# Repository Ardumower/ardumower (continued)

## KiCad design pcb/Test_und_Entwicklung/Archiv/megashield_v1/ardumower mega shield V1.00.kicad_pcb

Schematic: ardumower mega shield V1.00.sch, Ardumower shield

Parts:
C1, C2: 10uF
D1: LED
D2: MBR1045 schotky
D3: 5V
D4: 24V
D5: 1N4007
Dual1: MC33926
F1: FUSE
HC5: HC05_MODULE_ARDUMOWER_
JP1: JUMPER
K1: Tilt sens
P1: Perimeter
P2: Motor driver
P3: Bat charge
P4, P19: Mow Motor
P5: Motor sens
P6: Sonar C
P7: Sonar R
P8: Sonar L
P9: RC Remote
P10: ODO Left
P11: ODO Right
P12: User switch
P13: Lawn sens
P14: GPS RX
P15: DC/DC
P16: I2C
P17: Bumper
P18: 24V in
P20: SW_LED
P21: UART1
Q1: IRLIZ44N
R1, R6: 470R
R2, R4: 47K
R3, R5: 5K
R7, R8: 1K
R9, R10: 2M2
R11: 180
R12: 10K
R13: 470r
R14: 2k2
SHIELD1: ARDUINO_MEGA_SHIELD
SP1: SPEAKER
SW1: SW_PUSH
U1: DS1307_RTC_EMARTEE
U4: Traco TSR 1-2450

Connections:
+3.3V: JP1.1, SHIELD1.3V3
+5V: C2.1, Dual1.3 (Vdd), Dual1.6 (M1nD2), Dual1.15 (M2nD2), HC5.6, K1.1, P1.1, P2.6, P3.1, P4.1, P5.1, P6.1, P7.1, P8.1, P9.1, P10.1, P11.1, P12.1, P14.1, P16.1, P17.1, P20.1, P21.1, R8.2, R13.1, SHIELD1.5V, U1.2, U4.VO
+24V: C1.1, D2.2 (K), D5.2 (K), F1.1, F1.2, P15.1, P18.2 (PM), P19.1, R14.1, U4.VI
BatteryVoltage: R4.2, R5.1, SHIELD1.AD2
BumperLeft: P17.3, SHIELD1.39 (PG2)
BumperRight: P17.2, SHIELD1.37 (PC0)
Button: P20.3, SHIELD1.53 (PB0_(SS)), SW1.2
Buzzer: SHIELD1.35 (PC2), SP1.2
ChargeCurrent: P3.2, SHIELD1.AD9
ChargeVoltage: R2.2, R3.1, SHIELD1.AD8
GND: C1.2, C2.2, D1.2 (K), D3.2 (K), D4.2 (K), D5.1 (A), Dual1.2 (GND), Dual1.7 (M1D1), Dual1.16 (M2D1), HC5.5, K1.3, P1.4, P2.1, P3.5, P4.5, P5.4, P6.4, P7.4, P8.4, P9.6, P10.4, P11.4, P12.5, P14.4, P15.2 (PM), P16.4, P17.4, P18.1, P20.4, P21.4, Q1.S, R3.2, R5.2, R7.2, R12.1, SHIELD1.GND1, SHIELD1.GND2, SHIELD1.GND3, SHIELD1.GND4, SHIELD1.GND5, SP1.1, SW1.1, U1.1, U4.GND
GPS_RX: P14.2, SHIELD1.14 (TX3)
GPS_TX: P14.3, SHIELD1.15 (RX3)
LawnBackRecv: P13.2, SHIELD1.29 (PA7)
LawnBackSend: R9.2, SHIELD1.27 (PA5)
LawnFrontRecv: P13.4, SHIELD1.31 (PC6)
LawnFrontSend: R10.2, SHIELD1.33 (PC4)
Led: P20.2, R1.2, SHIELD1.49 (PL0)
Left perimeter: P1.3, SHIELD1.AD5
MotorEnable: Dual1.10 (EN), SHIELD1.30 (PC7)
MotorLeftDir: Dual1.4 (M1IN2), P2.5, SHIELD1.23 (PA1)
MotorLeftFault: Dual1.8 (M1nSF), SHIELD1.28 (PA6)
MotorLeftPWM: Dual1.5 (M1IN1), P2.4, SHIELD1.5
MotorLeftSense: Dual1.9 (M1FB), P5.2, SHIELD1.AD1
MotorMow: P4.2, R11.2, SHIELD1.2
MotorMowRpm: P4.4, SHIELD1.51 (PB2_(MOSI))
MotorMowSense: P4.3, SHIELD1.AD3
MotorRightDir: Dual1.13 (M2IN2), P2.3, SHIELD1.25 (PA3)
MotorRightFault: Dual1.17 (M2nSF), SHIELD1.32 (PC5)
MotorRightPWM: Dual1.14 (M2IN1), P2.2, SHIELD1.3
MotorRightSense: Dual1.18 (M2_FB), P5.3, SHIELD1.AD0
unnamed: P13.1, R9.1
unnamed: P13.3, R10.1
unnamed: Q1.G, R11.1, R12.2
unnamed: HC5.2, JP1.2
unnamed: D2.1 (A), P19.2 (PM), Q1.D
unnamed: D3.1 (A), R13.2
unnamed: D4.1 (A), R14.2
unnamed: D1.1 (A), R1.1
unnamed: P3.4, R4.1
unnamed: HC5.3, R6.2, R7.1
unnamed: P3.3, R2.1
OdometryLeft: P10.2, SHIELD1.AD12
OdometryLeft2: P10.3, SHIELD1.AD13
OdometryRight: P11.2, SHIELD1.AD14
OdometryRight2: P11.3, SHIELD1.AD15
RX1: P21.3, SHIELD1.19 (RX1)
RX2: HC5.4, R8.1, SHIELD1.17 (RX2)
RemoteMow: P9.2, SHIELD1.12
RemoteSpeed: P9.4, SHIELD1.10
RemoteSteer: P9.3, SHIELD1.11
RemoteSwitch: P9.5, SHIELD1.9
Right perimeter: P1.2, SHIELD1.AD4
SCL: P16.3, SHIELD1.21 (SCL), U1.4
SDA: P16.2, SHIELD1.20 (SDA), U1.3
SonarCenterEcho: P6.3, SHIELD1.40 (PG1)
SonarCenterTrigger: P6.2, SHIELD1.38 (PD7)
SonarLeftEcho: P8.3, SHIELD1.36 (PC1)
SonarLeftTrigger: P8.2, SHIELD1.34 (PC3)
SonarRightEcho: P7.3, SHIELD1.44 (PL5)
SonarRightTrigger: P7.2, SHIELD1.42 (PL7)
TX1: P21.2, SHIELD1.18 (TX1)
TX2: R6.1, SHIELD1.16 (TX2)
Tilt: K1.2 (PM), SHIELD1.47 (PL2)
UserSwitch1: P12.2, SHIELD1.41 (PG0)
UserSwitch2: P12.3, SHIELD1.43 (PL6)
UserSwitch3: P12.4, SHIELD1.45 (PL4)

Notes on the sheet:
Sonar HC SR-04
Battery Charge
Perimeter coil
Motor Driver
Odometry left
Odometry right
Lawn sensor
Tilt sensor
GPS
Bumper

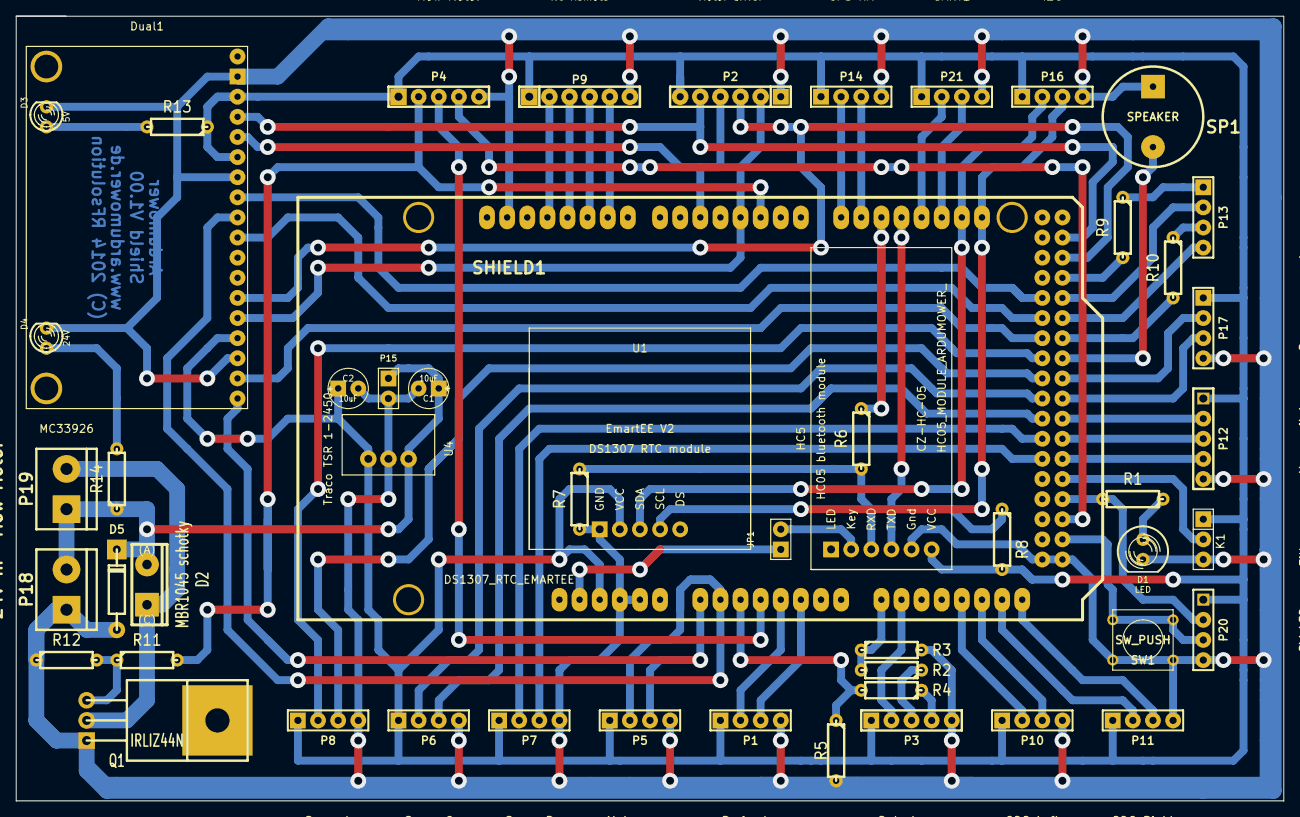
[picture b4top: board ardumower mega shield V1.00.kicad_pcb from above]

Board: 2 copper layers, 160.0 x 99.1 mm, 52 parts (0 on the bottom side), 67 nets.

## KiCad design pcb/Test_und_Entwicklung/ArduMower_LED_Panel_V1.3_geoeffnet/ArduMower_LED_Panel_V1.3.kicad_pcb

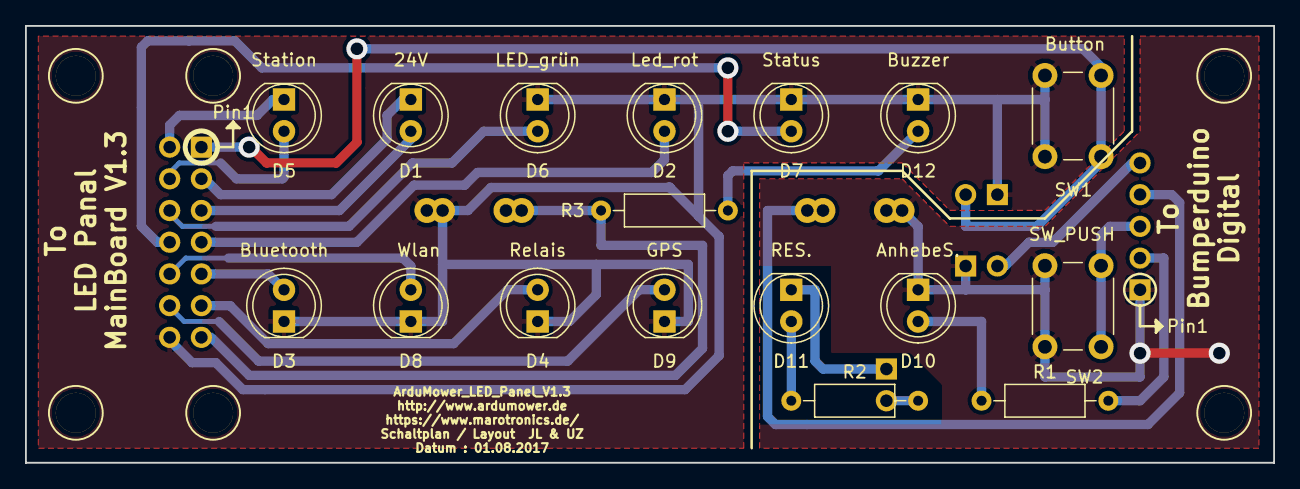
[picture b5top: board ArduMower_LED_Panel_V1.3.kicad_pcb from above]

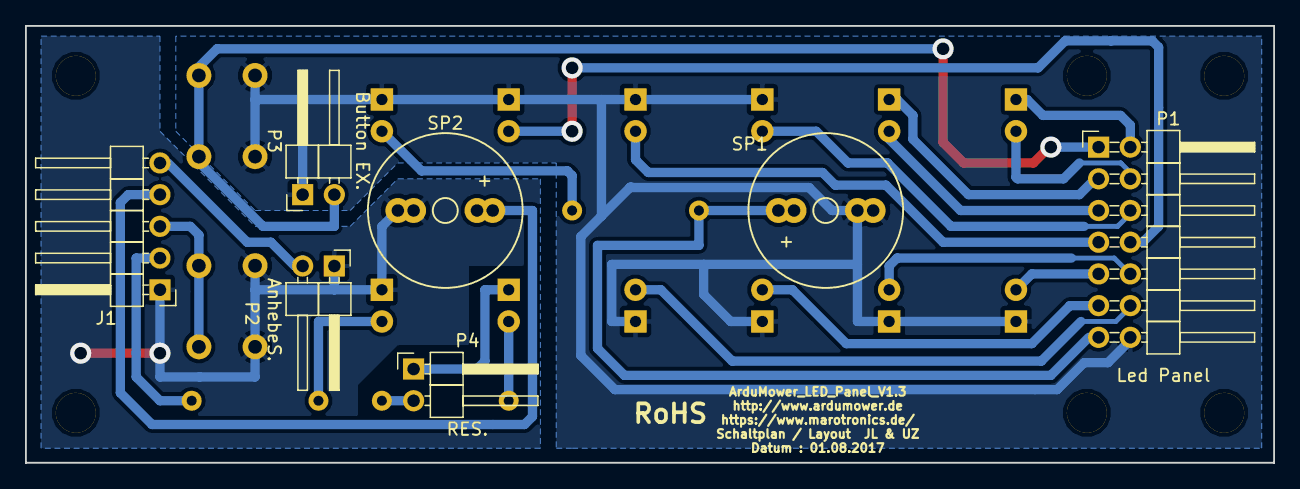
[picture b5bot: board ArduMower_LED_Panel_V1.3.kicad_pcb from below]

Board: 2 copper layers, 100.0 x 35.0 mm, 30 parts (7 on the bottom side), 24 nets.

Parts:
B1, B2, B3, B4, B5, B6: Bohrloch_3,2mm_ohne_Kupferfläche; Bohrloch_3,2mm
D1: 24V; LED_D5.0mm
D2: Led_rot; LED_D5.0mm
D3: Bluetooth; LED_D5.0mm
D4: Relais; LED_D5.0mm
D5: Station; LED_D5.0mm
D6: LED_grün; LED_D5.0mm
D7: Status; LED_D5.0mm
D8: Wlan; LED_D5.0mm
D9: GPS; LED_D5.0mm
D10: AnhebeS.; LED_D5.0mm
D11: RES.; LED_D5.0mm
D12: Buzzer; LED_D5.0mm
J1: CONN_01X05; Pin_Header_Angled_1x05_Pitch2.54mm
P1: Led Panel; Pin_Header_Angled_2x07_Pitch2.54mm
P2: AnhebeS.; Pin_Header_Angled_1x02_Pitch2.54mm
P3: Button EX.; Pin_Header_Angled_1x02_Pitch2.54mm
P4: RES.; Pin_Header_Angled_1x02_Pitch2.54mm
R1, R2, R3: 220; R_Axial_DIN0207_L6.3mm_D2.5mm_P10.16mm_Horizontal
SP1: Buzzer; Buzzer_12x9.5RM7.6_RM5.0
SP2: SPEAKER; Buzzer_12x9.5RM7.6_RM5.0
SW1: Button; SW_PUSH_6mm_h8.5mm
SW2: SW_PUSH; SW_PUSH_6mm_h8.5mm

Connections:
/24V: D1.2, P1.5
/24V_GND: D1.1, P1.3
/Bluetooth: D3.2, P1.9
/Buzzer: P1.13, R3.2, SP1.2
/Duo_Led_Rot: D2.2, P1.7
/Duo_Led_grün: D6.2, P1.6
/GPS_LED: D9.2, P1.12
/Led_Status: D7.2, P1.8
/PinCharging_Enable: D4.2, P1.11
/StationLed: D5.2, P1.4
/StationLed_GND: D5.1, P1.2
/Taster: P1.1, P3.2, SW1.2
/Wlan: D8.2, P1.10
GND: D2.1, D3.1, D4.1, D6.1, D7.1, D8.1, D9.1, D12.1, P1.14, P3.1, SP1.1, SW1.1
GNDD: D10.1, J1.1, P2.1, SP2.1, SW2.1
unnamed: D10.2, R1.1
unnamed: D11.1, P4.1
unnamed: D11.2, R2.1
unnamed: D12.2, R3.1
unnamed: J1.2, R1.2
unnamed: J1.3, SW2.2
unnamed: J1.4, SP2.2
unnamed: J1.5, P2.2
unnamed: P4.2, R2.2

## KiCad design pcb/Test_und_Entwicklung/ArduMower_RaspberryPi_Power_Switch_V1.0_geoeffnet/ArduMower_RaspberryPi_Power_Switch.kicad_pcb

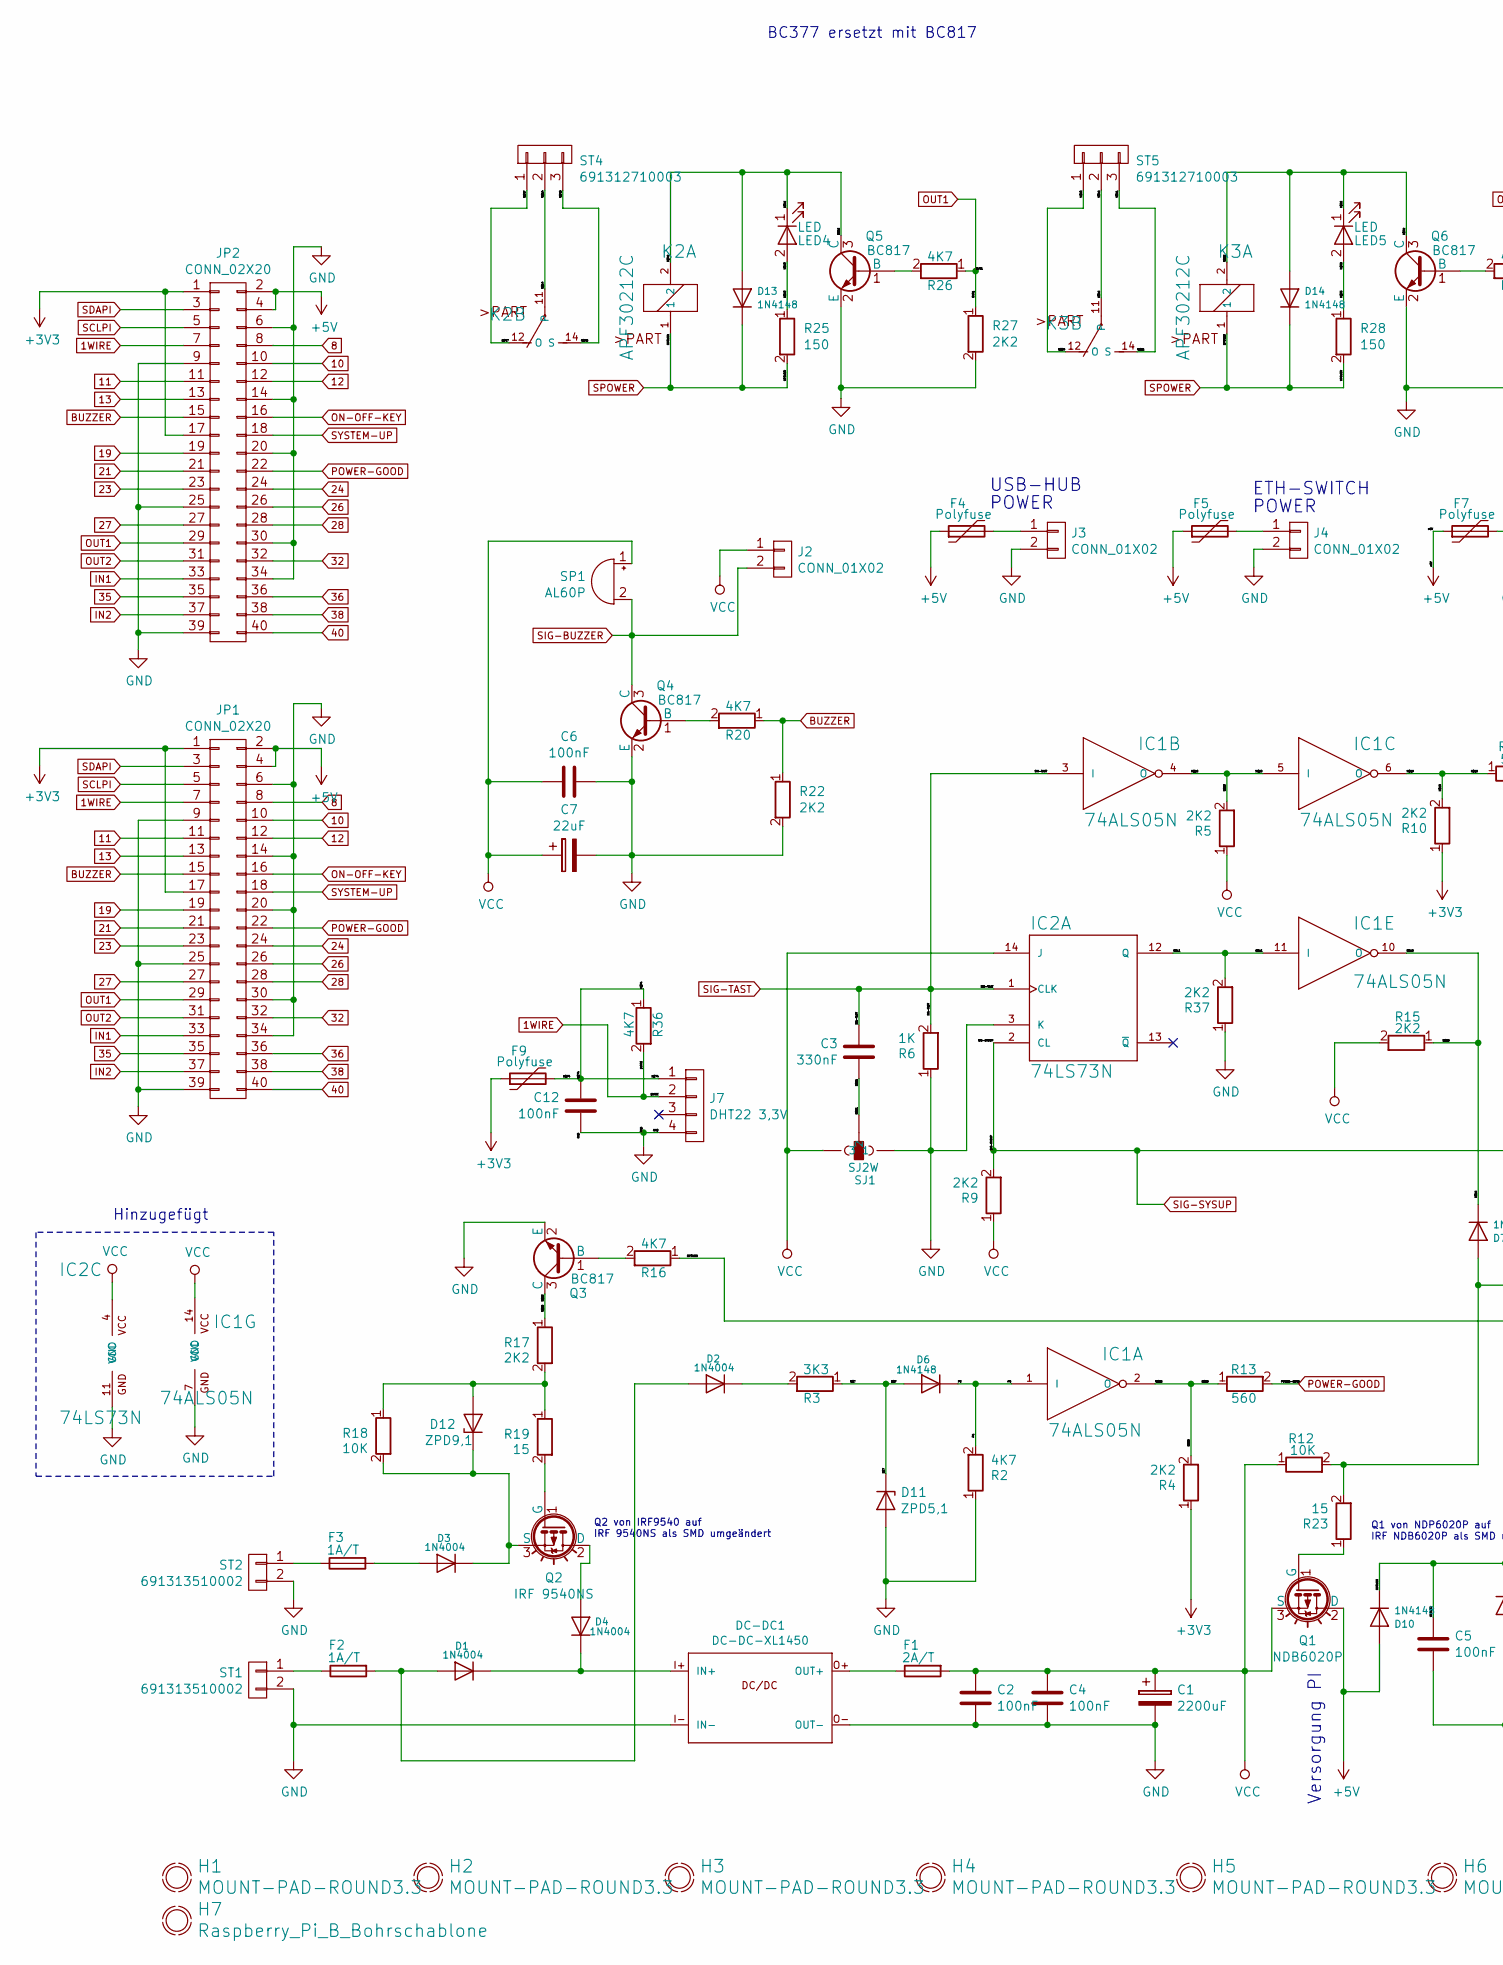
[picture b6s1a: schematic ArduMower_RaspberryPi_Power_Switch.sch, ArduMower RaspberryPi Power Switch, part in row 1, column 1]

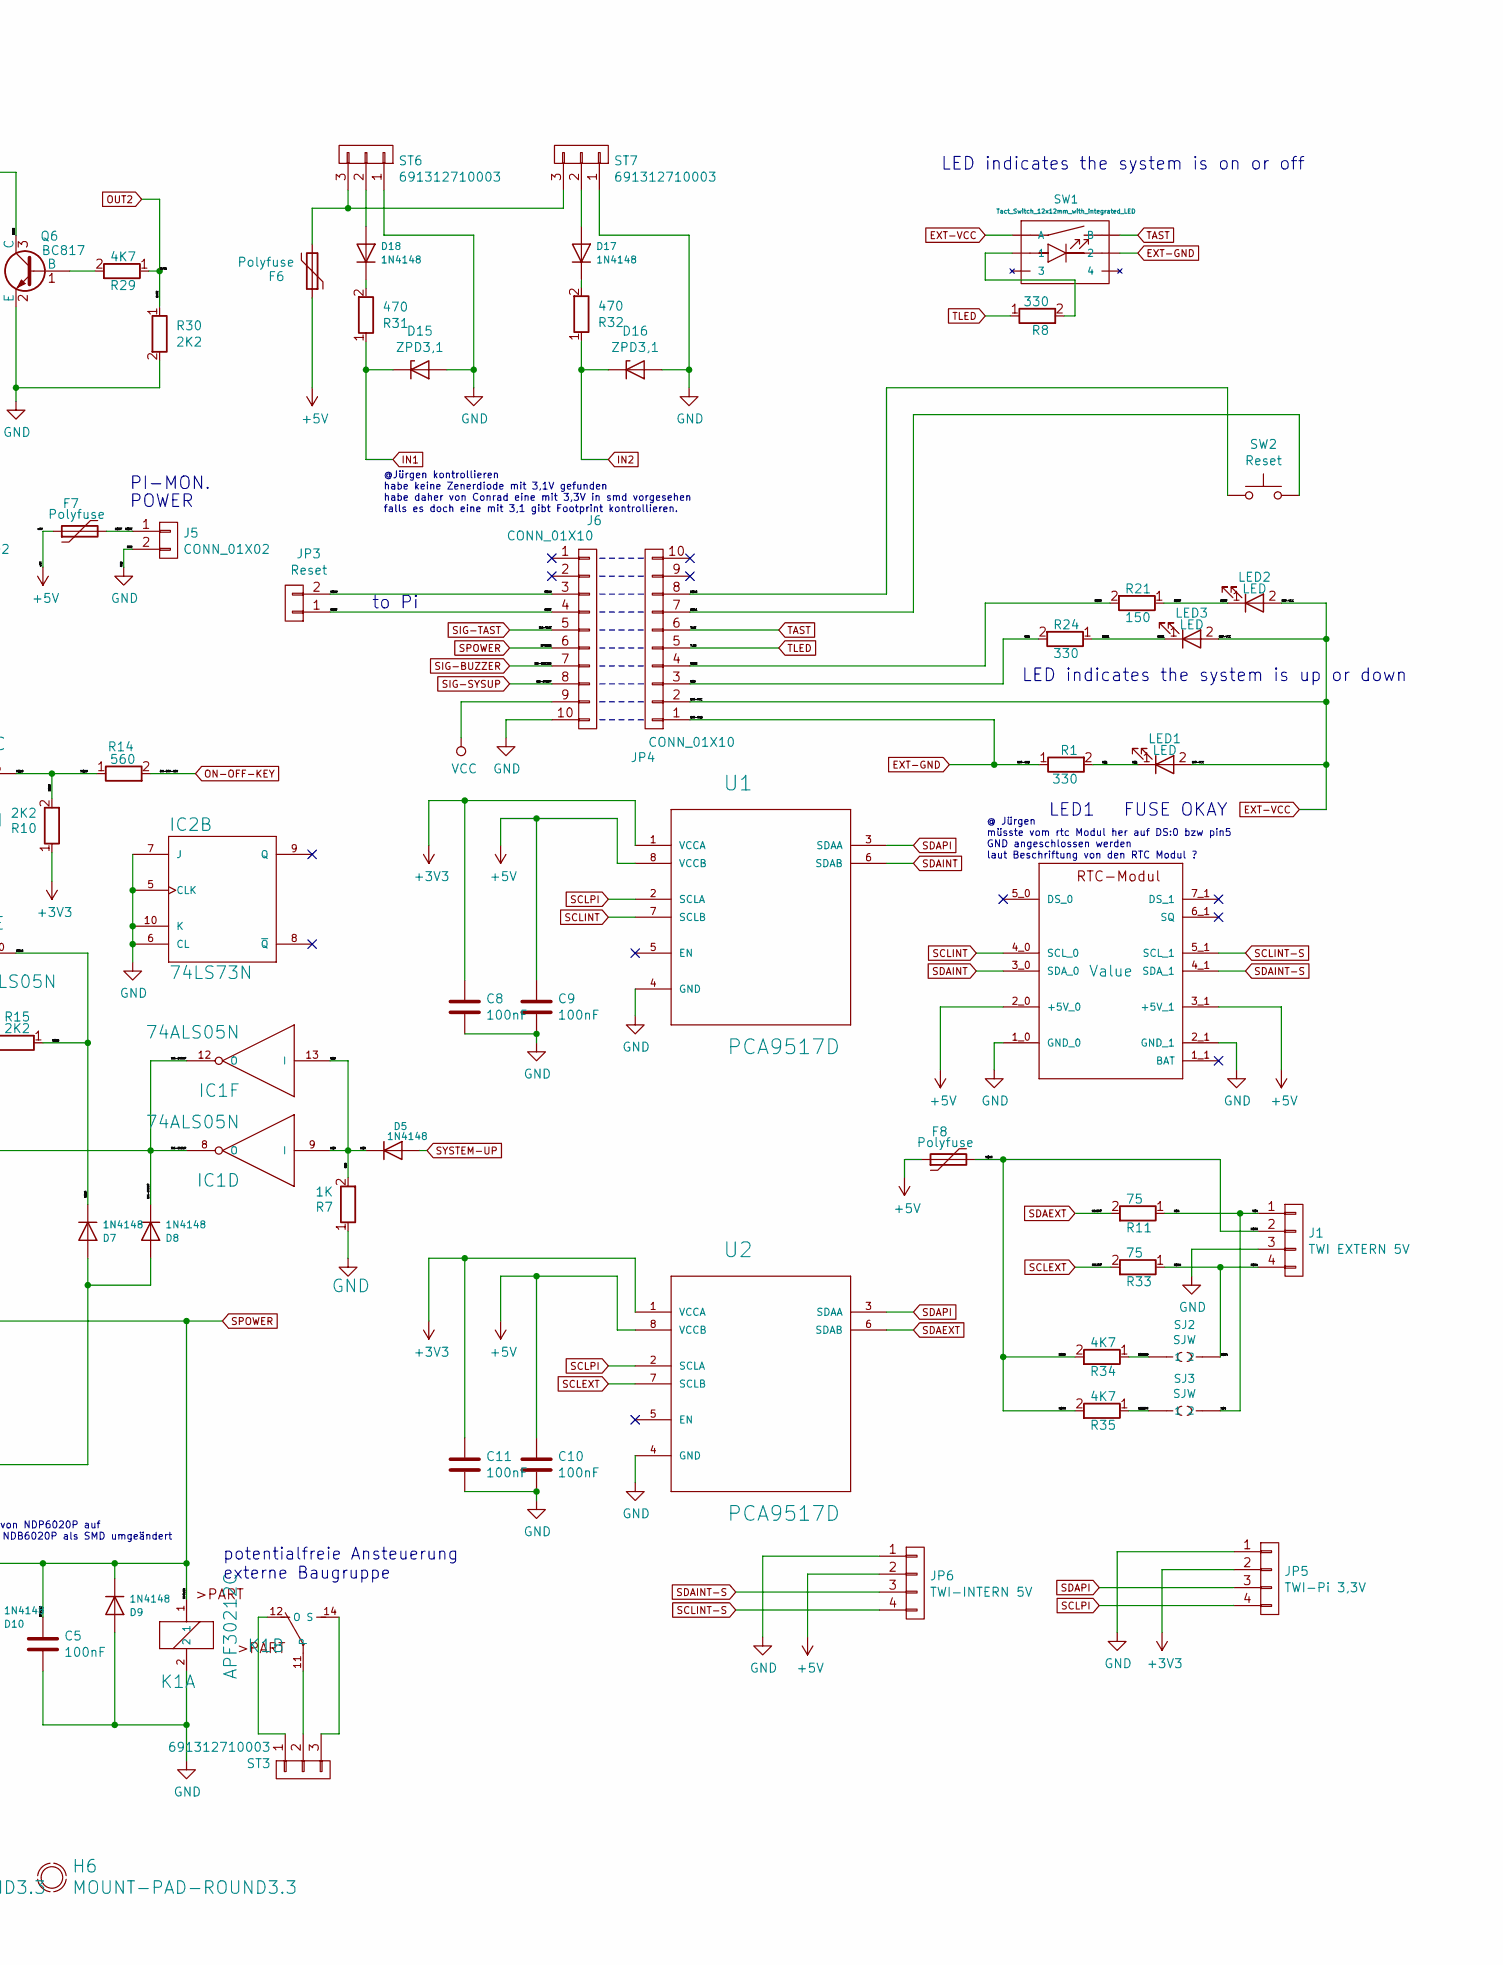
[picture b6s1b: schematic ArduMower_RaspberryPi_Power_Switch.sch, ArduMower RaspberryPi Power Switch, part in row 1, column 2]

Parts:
C1: 2200uF; C_Radial_D10_L20_P5-7.5
C2, C4, C5, C6, C8, C9, C10, C11, C12: 100nF; C_0805
C3: 330nF; c_elec_5x5.8
C7: 22uF; C_Radial_D10_L20_P2.5-5
D1, D2, D3, D4: 1N4004; DO-214AB
D5, D6, D7, D8, D9, D10, D13, D14, D17, D18: 1N4148; MiniMELF_Standard
D11: ZPD5,1; MiniMELF_Standard
D12: ZPD9,1; MiniMELF_Standard
D15, D16: ZPD3,1; MiniMELF_Standard
DC-DC1: DC-DC-XL1450; DCDC-XL1450_Bohrlöcher_und_Rahmen
F1: 2A/T; Sicherungs_Sockel_für_TR5_TE5
F2, F3: 1A/T; Sicherungs_Sockel_für_TR5_TE5
F4, F5, F6, F7, F8, F9: Polyfuse
H1, H2, H3, H4, H5, H6: MOUNT-PAD-ROUND3.3
H7: Raspberry_Pi_B_Bohrschablone; Raspberry_Pi_B_Bohrschablone_Rueckseite
IC1: 74ALS05N; DIP-14__300
IC2: 74LS73N; DIP-14__300
J1: TWI EXTERN 5V; TerminalBlock_Pheonix_MPT-2.54mm_4pol
J2, J3, J4, J5: CONN_01X02; Anschlussklemme_2P_RM2,54_RM5,08
J6: CONN_01X10; Molex_KK-6410-10_10x2.54mm_Straight
J7: DHT22 3,3V; TerminalBlock_Pheonix_MPT-2.54mm_4pol
JP1, JP2: CONN_02X20; Socket_Strip_Straight_2x20
JP3: Reset; Pin_Header_Angled_1x02
JP4: CONN_01X10; Molex_KK-6410-10_10x2.54mm_Straight
JP5: TWI-Pi 3,3V; TerminalBlock_Pheonix_MPT-2.54mm_4pol
JP6: TWI-INTERN 5V; Molex_KK-6410-04_04x2.54mm_Straight
K1, K2, K3: APF30212C; relay_34.51
LED1, LED2, LED3, LED4, LED5: LED; LED_1206
MD1: Tiny_RTC_Modul
Q1: NDB6020P; TO-263-3Lead
Q2: IRF 9540NS; d2-pak
Q3, Q4, Q5, Q6: BC817; SOT-23
R1, R8, R24: 330; R_1206
R2, R16, R20, R26, R29, R34, R35, R36: 4K7; R_1206
R3: 3K3; R_1206
R4, R5, R9, R10, R15, R17, R22, R27, R30, R37: 2K2; R_1206
R6, R7: 1K; R_1206
R11, R33: 75; R_1206
R12, R18: 10K; R_1206
R13, R14: 560; R_1206
R19, R23: 15; R_1206
R21, R25, R28: 150; R_1206
R31, R32: 470; R_1206
SJ1: SJ2W; SJ_2W
SJ2, SJ3: SJW; SJ
SP1: AL60P; Buzzer_12x9.5RM7.6_RM5.0
ST1, ST2: 691313510002; mstba_2,5%2f2-g-5,08
ST3, ST4, ST5, ST6, ST7: 691312710003; mstba_2,5%2f3-g-5,08
SW1: Tact_Switch_12x12mm_with_integrated_LED
SW2: Reset; SW_SPST_PTS645
U1, U2: PCA9517D; SOIC127P600X175-8N

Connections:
1WIRE: J7.2, JP1.7, JP2.7, R36.2
8: JP1.8, JP2.8
10: JP1.10, JP2.10
11: JP1.11, JP2.11
12: JP1.12, JP2.12
13: JP1.13, JP2.13
19: JP1.19, JP2.19
21: JP1.21, JP2.21
23: JP1.23, JP2.23
24: JP1.24, JP2.24
26: JP1.26, JP2.26
27: JP1.27, JP2.27
28: JP1.28, JP2.28
32: JP1.32, JP2.32
35: JP1.35, JP2.35
36: JP1.36, JP2.36
38: JP1.38, JP2.38
40: JP1.40, JP2.40
+3V3: C8.1, C11.1, F9.1, JP1.1, JP1.17, JP2.1, JP2.17, JP5.2, R4.1, R10.1, U1.1 (VCCA), U2.1 (VCCA)
+5V: C9.1, C10.1, D10.2 (A), F4.1, F5.1, F6.1, F7.1, F8.1, JP1.2, JP1.4, JP2.2, JP2.4, JP6.2, MD1.2_0 (+5V_0), MD1.3_1 (+5V_1), Q1.2 (D), U1.8 (VCCB), U2.8 (VCCB)
/N$1: LED1.1 (K), R1.2
/N$4: J1.1, R11.1, SJ3.2
/N$7: D6.2 (A), D11.1 (K), R3.1
/N$8: JP4.3, R24.2
/N$9: D5.1 (K), IC1.9 (I), IC1.13 (I), R7.2
/N$10: IC1.4 (O), IC1.5 (I), R5.2
/N$11: IC1.11 (I), IC2.12 (Q), R37.2
/N$14: K2.11, ST4.2
/N$15: D7.1 (K), IC1.10 (O), R15.1
/N$19: IC1.6 (O), R10.2, R14.1
/N$20: IC1.2 (O), R4.2, R13.1
/N$21: C3.2, SJ1.2
/N$23: JP4.4, R21.2
/N$26: Q3.3 (C), R17.1
/N$27: LED2.1 (K), R21.1
/N$31: LED3.1 (K), R24.1
/N$40: JP4.8, SW2.1
/N$41: JP4.7, SW2.2
/N$42: D13.2 (A), K2.2, LED4.1 (K), Q5.3 (C)
/N$43: LED4.2 (A), R25.1
/N$46: K3.11, ST5.2
/N$47: K2.12 (O), ST4.1
/N$48: K2.14 (S), ST4.3
/N$50: K3.12 (O), ST5.1
/N$51: K3.14 (S), ST5.3
/N$52: D14.2 (A), K3.2, LED5.1 (K), Q6.3 (C)
/N$53: LED5.2 (A), R28.1
/N$57: F7.2, J5.1
/N$64: J1.4, R33.1, SJ2.2
/N$66: F8.2, J1.2, R34.2, R35.2
/N$67: J6.4, JP3.1
/N$68: J6.3, JP3.2
/N$69: R34.1, SJ2.1
/N$70: R35.1, SJ3.1
/N$74: C12.1, F9.2, J7.1, R36.1
/PG: D6.1 (K), IC1.1 (I), R2.2
BUZZER: JP1.15, JP2.15, R20.1, R22.1
EXT-GND: JP4.1, R1.1, SW1.2
EXT-VCC: JP4.2, LED1.2 (A), LED2.2 (A), LED3.2 (A), SW1.A
GND: C1.2, C2.2, C4.2, C5.2, C6.2, C7.2, C8.2, C9.2, C10.2, C11.2, C12.2, D9.2 (A), D11.2 (A), D15.2 (A), D16.2 (A), DC-DC1.I- (IN-), DC-DC1.O- (OUT-), IC1.7 (GND), IC2.3 (K), IC2.5 (CLK), IC2.6 (CL), IC2.7 (J), IC2.10 (K), IC2.11 (GND), J1.3, J3.2, J4.2, J5.2, J6.10, J7.4, JP1.6, JP1.9, JP1.14, JP1.20, JP1.25, JP1.30, JP1.34, JP1.39, JP2.6, JP2.9, JP2.14, JP2.20, JP2.25, JP2.30, JP2.34, JP2.39, JP5.1, JP6.1, K1.2, MD1.1_0 (GND_0), MD1.2_1 (GND_1), Q3.2 (E), Q4.2 (E), Q5.2 (E), Q6.2 (E), R2.1, R6.1, R7.1, R22.2, R27.2, R30.2, R37.1, SJ1.1, ST1.2, ST2.2, ST6.1, ST7.1, U1.4 (GND), U2.4 (GND)
IN1: D15.1 (K), JP1.33, JP2.33, R31.1
IN2: D16.1 (K), JP1.37, JP2.37, R32.1
unnamed: D1.1 (K), D4.1 (K), DC-DC1.I+ (IN+)
unnamed: D1.2 (A), D2.2 (A), F2.2
unnamed: D2.1 (K), R3.2
unnamed: D3.2 (A), F3.2
unnamed: D4.2 (A), Q2.2 (D)
unnamed: D7.2 (A), D8.2 (A), R12.2, R23.2
unnamed: D3.1 (K), D12.1 (K), Q2.3 (S), R18.2
unnamed: D12.2 (A), R17.2, R18.1, R19.1
unnamed: D17.1 (K), R32.2
unnamed: D17.2 (A), ST7.2
unnamed: D18.1 (K), R31.2
unnamed: D18.2 (A), ST6.2
unnamed: DC-DC1.O+ (OUT+), F1.1
unnamed: F2.1, ST1.1
unnamed: F3.1, ST2.1
unnamed: F4.2, J3.1
unnamed: F5.2, J4.1
unnamed: F6.2, ST6.3, ST7.3
unnamed: K1.11, ST3.2
unnamed: K1.12 (O), ST3.1
unnamed: K1.14 (S), ST3.3
unnamed: Q1.1 (G), R23.1
unnamed: Q2.1 (G), R19.2
unnamed: Q3.1 (B), R16.2
unnamed: Q4.1 (B), R20.2
unnamed: Q5.1 (B), R26.2
unnamed: Q6.1 (B), R29.2
unnamed: R8.2, SW1.1
ON-OFF-KEY: JP1.16, JP2.16, R14.2
OUT1: JP1.29, JP2.29, R26.1, R27.1
OUT2: JP1.31, JP2.31, R29.1, R30.1
POWER-GOOD: JP1.22, JP2.22, R13.2
SCLEXT: R33.2, U2.7 (SCLB)
SCLINT: MD1.4_0 (SCL_0), U1.7 (SCLB)
SCLINT-S: JP6.4, MD1.5_1 (SCL_1)
SCLPI: JP1.5, JP2.5, JP5.4, U1.2 (SCLA), U2.2 (SCLA)
SDAEXT: R11.2, U2.6 (SDAB)
SDAINT: MD1.3_0 (SDA_0), U1.6 (SDAB)
SDAINT-S: JP6.3, MD1.4_1 (SDA_1)
SDAPI: JP1.3, JP2.3, JP5.3, U1.3 (SDAA), U2.3 (SDAA)
SIG-BUZZER: J2.2, J6.7, Q4.3 (C), SP1.2 (+)
SIG-SYSUP: D8.1 (K), IC1.8 (O), IC1.12 (O), IC2.2 (CL), J6.8, R9.2
SIG-TAST: C3.1, IC1.3 (I), IC2.1 (CLK), J6.5, R6.2
SPOWER: C5.1, D9.1 (K), D10.1 (K), D13.1 (K), D14.1 (K), J6.6, K1.1, K2.1, K3.1, R16.1, R25.2, R28.2
SYSTEM-UP: D5.2 (A), JP1.18, JP2.18
TAST: JP4.6, SW1.B
TLED: JP4.5, R8.1
VCC: C1.1, C2.1, C4.1, C6.1, C7.1, F1.2, IC1.14 (VCC), IC2.4 (VCC), IC2.14 (J), J2.1, J6.9, Q1.3 (S), R5.1, R9.1, R12.1, R15.2, SJ1.3, SP1.1 (-)

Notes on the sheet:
LED1 FUSE OKAY
LED indicates the system is on or off
Versorgung PI
potentialfreie Ansteuerung externe Baugruppe
LED indicates the system is up or down
PI-MON.
ETH-SWITCH
USB-HUB
POWER
to Pi
BC377 ersetzt mit BC817
@Jürgen kontrollieren habe keine Zenerdiode mit 3,1V gefunden habe daher von Conrad eine mit 3,3V in smd vorgesehen falls es doch eine mit 3,1 gibt Footprint kontrollieren.
@ Jürgen müsste vom rtc Modul her auf DS:0 bzw pin5 GND angeschlossen werden laut Beschriftung von den RTC Modul ?
Q2 von IRF9540 auf IRF 9540NS als SMD umgeändert
Q1 von NDP6020P auf IRF NDB6020P als SMD umgeändert
Hinzugefügt

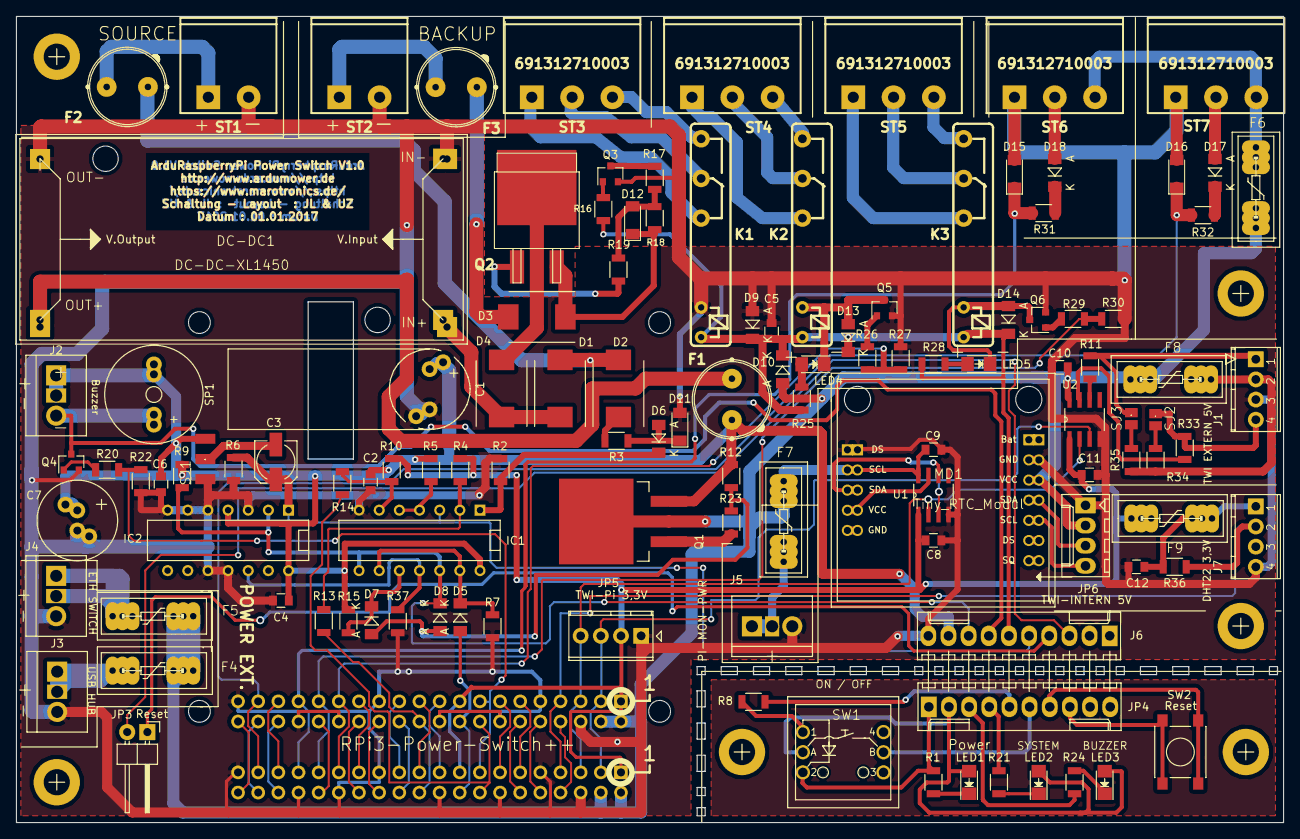
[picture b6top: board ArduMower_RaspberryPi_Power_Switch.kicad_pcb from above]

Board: 2 copper layers, 159.7 x 101.6 mm, 129 parts (0 on the bottom side), 110 nets.
